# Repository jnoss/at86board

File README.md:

at86board
=========

eagle files for an at86rf233 (802.15.4 transceiver) board with antenna to SPI

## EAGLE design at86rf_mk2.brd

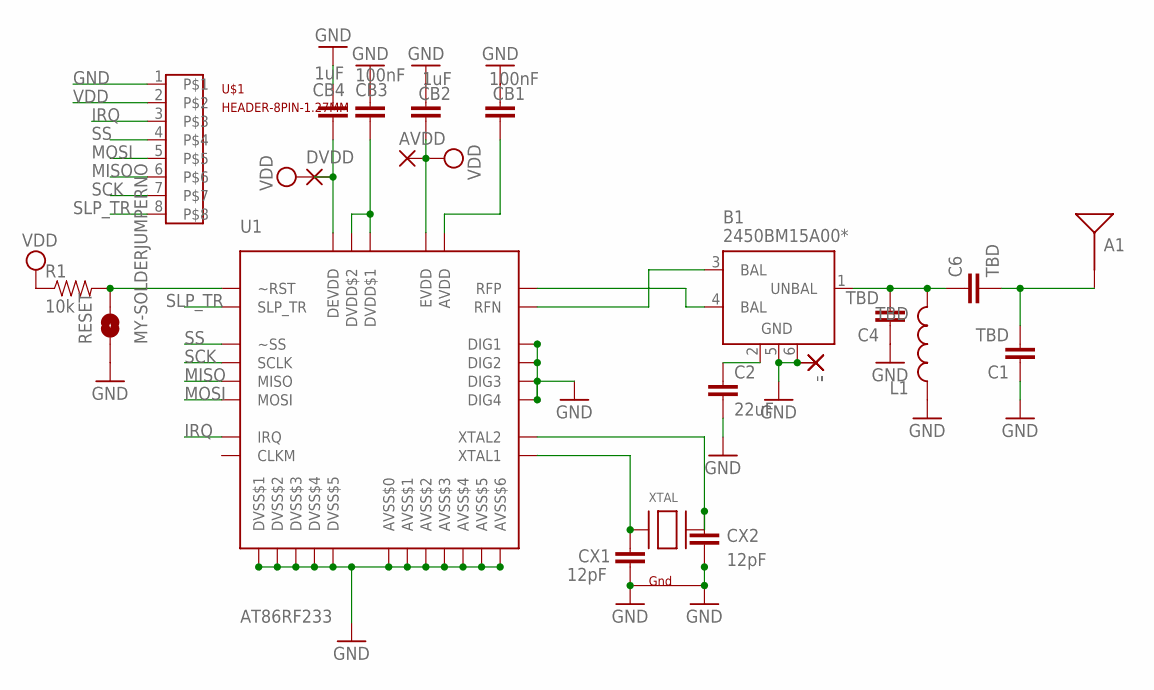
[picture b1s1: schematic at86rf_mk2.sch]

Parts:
': VIAPADNOTHERMAL; VIAPAD13MIL-NOTHERMAL
'': VIAPADNOTHERMAL; VIAPAD13MIL-NOTHERMAL
A1: ANTENNA2SMD5; ANTENNA-CHIP5
AVDD: VIAPADNOPASTE; PAD-1-NOPASTE
B1: 2450BM15A00*; 2450BM15A0002
C1, C4, C6: TBD; 0402-CAP
C2: 22uF; 0402-CAP
CB1, CB3: 100nF; 0402-CAP
CB2, CB4: 1uF; 0603-CAP
CX1, CX2: 12pF; 0402-CAP
DVDD: VIAPADNOPASTE; PAD-1-NOPASTE
L1: TBD; C0402
R1: 10k; 0402-RES
RESET: MY-SOLDERJUMPERNO; SJ_2S-NO
U1: AT86RF233; QFN-32
U$1: HEADER-8PIN-1.27MM; 1X08-1.27MM
XTAL: XTAL-4-3225; NX3225

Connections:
GND: '.1, ''.1, B1.5 (GND), B1.6 (GND), C1.1, C2.2, C4.1, CB1.1, CB2.1, CB3.1, CB4.1, CX1.2, CX2.2, L1.1, RESET.1, U1.1 (DIG3), U1.2 (DIG4), U1.3 (AVSS$1), U1.6 (AVSS$2), U1.7 (DVSS$1), U1.9 (DIG1), U1.10 (DIG2), U1.12 (DVSS$2), U1.16 (DVSS$3), U1.18 (DVSS$4), U1.21 (DVSS$5), U1.27 (AVSS$3), U1.30 (AVSS$4), U1.31 (AVSS$5), U1.32 (AVSS$6), U1.EP (AVSS$0), U$1.1, XTAL.2 (G2), XTAL.4 (G1)
IRQ: U1.24 (IRQ), U$1.3
MISO: U1.20 (MISO), U$1.6
MOSI: U1.22 (MOSI), U$1.5
unnamed: CB3.2, U1.13 (DVDD$1), U1.14 (DVDD$2)
unnamed: CB1.2, U1.29 (AVDD)
unnamed: CX2.1, U1.25 (XTAL2), XTAL.3 (X2)
unnamed: CX1.1, U1.26 (XTAL1), XTAL.1 (X1)
unnamed: B1.3 (BAL), U1.5 (RFN)
unnamed: B1.4 (BAL), U1.4 (RFP)
unnamed: B1.1 (UNBAL), C4.2, C6.1, L1.2
unnamed: R1.2, RESET.2, U1.8 (~RST)
unnamed: A1.FEED, C1.2, C6.2
unnamed: B1.2 (GND), C2.1
SCK: U1.19 (SCLK), U$1.7
SLP_TR: U1.11 (SLP_TR), U$1.8
SS: U1.23 (~SS), U$1.4
VDD: AVDD.P$1, CB2.2, CB4.2, DVDD.P$1, R1.1, U1.15 (DEVDD), U1.28 (EVDD), U$1.2

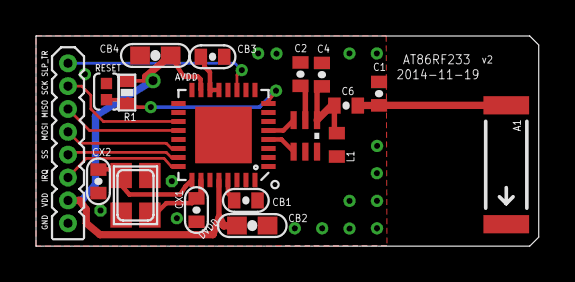
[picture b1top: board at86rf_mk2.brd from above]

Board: 2 copper layers, 27.9 x 11.7 mm, 22 parts (0 on the bottom side), 18 nets.

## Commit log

2014-11-23 add submodule for autopreviews
2014-11-23 add gitignore
2014-11-23 add board and schematic files
2014-11-23 sync
2014-11-23 test auto preview diff
2014-11-23 test
2014-11-23 test2
2014-11-23 change commit for autopreview submodule

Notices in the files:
parts and their libraries:
SparkFun-RF: Licensing: CC v3.0 Share-Alike You are welcome to use this library for commercial purposes.
